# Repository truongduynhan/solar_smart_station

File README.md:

<h1 align="center">Balanced Solar Charger</h1>

<p align="center" width="100%">
  
</p>

***

<p align="center">
  
&nbsp; &nbsp; &nbsp; &nbsp;
  
</p>

***

## SPECIFICATIONS

| Parameter | Value | 
| --- | --- |
| Dimensions | 57.75 × 39.5 mm |

***

## DIRECTORY STRUCTURE

    .
    ├─ Computations       # Misc calculations
    ├─ HTML               # HTML files for generated webpage
    ├─ Images             # Pictures and renders
    │
    ├─ kibot_resources    # External resources for KiBot
    │  ├─ colors          # Color theme for KiCad
    │  ├─ fonts           # Fonts used in the project
    │  ├─ scripts         # External scripts used with KiBot
    │  └─ templates       # Templates for KiBot generated reports
    │
    ├─ kibot_yaml         # KiBot YAML config files
    ├─ KiRI               # KiRI (PCB diff viewer) files
    │
    ├─ lib                # KiCad footprint and symbol libraries
    │  ├─ 3d_models       # Component 3D models
    │  ├─ lib_fp          # Footprint libraries
    │  └─ lib_sym         # Symbol libraries
    │
    ├─ Logos              # Logos
    │
    ├─ Manufacturing      # Assembly and fabrication documents
    │  ├─ Assembly        # Assembly documents (BoM, pos, notes)
    │  │
    │  └─ Fabrication     # Fabrication documents (ZIP, notes)
    │     ├─ Drill Tables # CSV drill tables
    │     └─ Gerbers      # Gerbers
    │
    ├─ Report             # Reports for ERC/DRC
    ├─ Schematic          # PDF of schematic
    ├─ Templates          # Title block templates
    ├─ Testing
    │  └─ Testpoints      # Testpoints tables      
    │
    └─ Variants           # Outputs for assembly variants

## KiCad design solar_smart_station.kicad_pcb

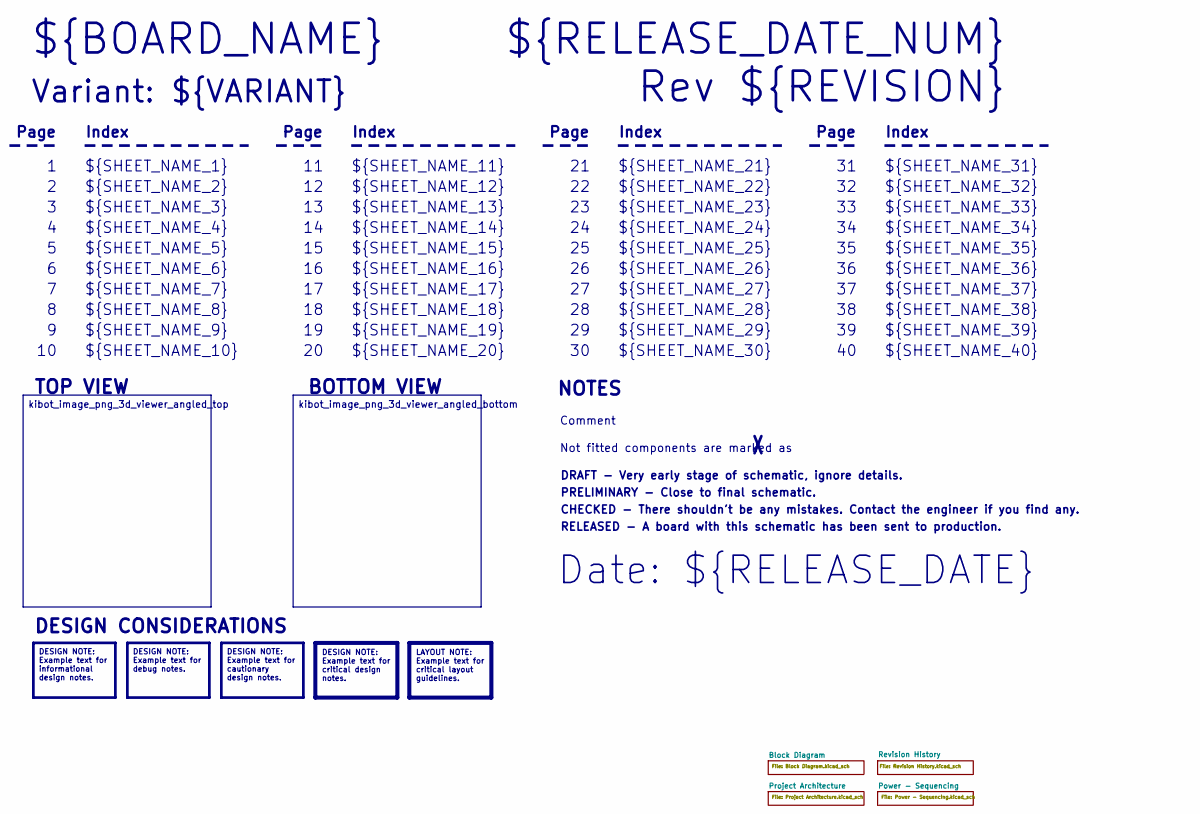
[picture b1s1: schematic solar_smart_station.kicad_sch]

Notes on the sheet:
Variant: ${VARIANT}
RELEASED - A board with this schematic has been sent to production.
${SHEET_NAME_24}
Index
Page
PRELIMINARY - Close to final schematic.
${SHEET_NAME_22}
DRAFT - Very early stage of schematic, ignore details.
${SHEET_NAME_12}
${SHEET_NAME_8}
${SHEET_NAME_2}
${SHEET_NAME_5}
${SHEET_NAME_20}
${SHEET_NAME_23}
${RELEASE_DATE_NUM}
${SHEET_NAME_35}
Not fitted components are marked as
${SHEET_NAME_11}
${SHEET_NAME_6}
${SHEET_NAME_37}
${SHEET_NAME_26}
${SHEET_NAME_36}
Rev ${REVISION}
${SHEET_NAME_15}
CHECKED - There shouldn't be any mistakes. Contact the engineer if you find any.
BOTTOM VIEW
${SHEET_NAME_14}
${SHEET_NAME_21}
${SHEET_NAME_17}
${SHEET_NAME_18}
Date: ${RELEASE_DATE}
${SHEET_NAME_7}
${SHEET_NAME_31}
${BOARD_NAME}
NOTES
${SHEET_NAME_40}
${SHEET_NAME_39}
${SHEET_NAME_32}
${SHEET_NAME_1}
${SHEET_NAME_9}

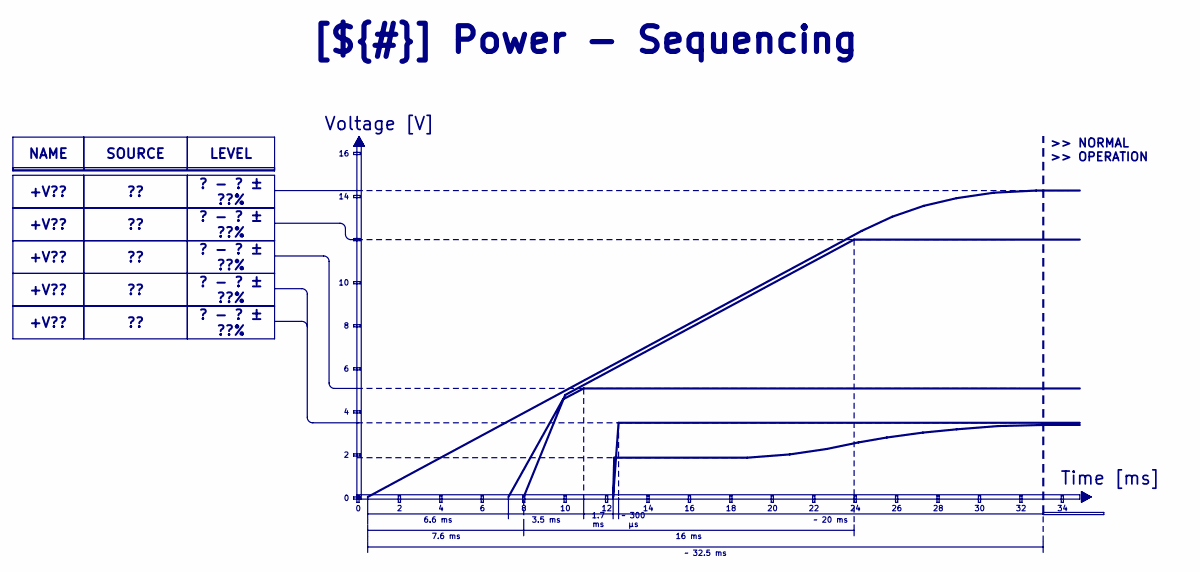
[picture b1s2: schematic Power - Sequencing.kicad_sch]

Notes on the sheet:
Voltage [V]
>> NORMAL >> OPERATION
Time [ms]
3.5 ms
7.6 ms
? - ? ± ??%
~ 300 μs
1.7 ms
16 ms
+V??
LEVEL
NAME
~ 20 ms
SOURCE
[${#}] ${TITLE}
6.6 ms
~ 32.5 ms

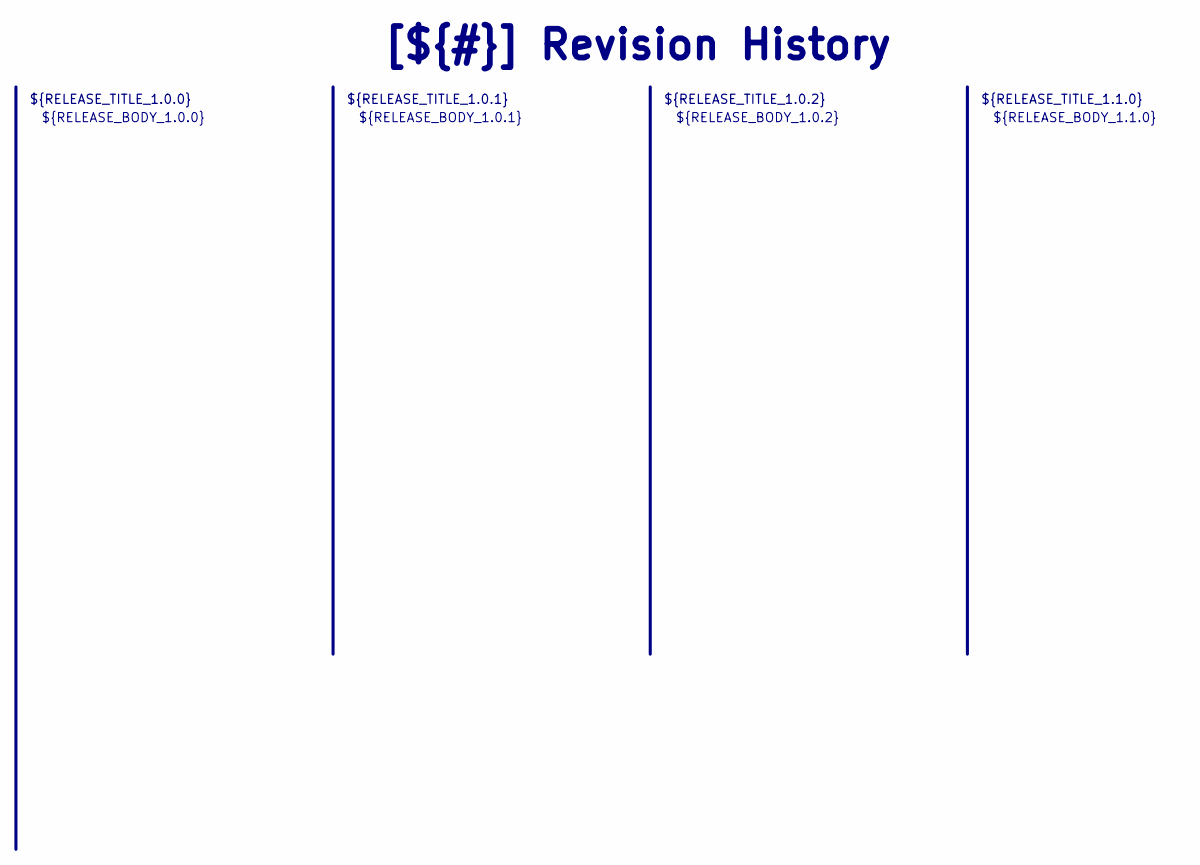
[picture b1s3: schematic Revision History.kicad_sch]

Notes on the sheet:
${RELEASE_BODY_1.1.0}
[${#}] ${TITLE}
${RELEASE_BODY_1.0.0}
${RELEASE_TITLE_1.0.2}
${RELEASE_BODY_1.0.2}
${RELEASE_BODY_1.0.1}
${RELEASE_TITLE_1.0.0}
${RELEASE_TITLE_1.0.1}
${RELEASE_TITLE_1.1.0}

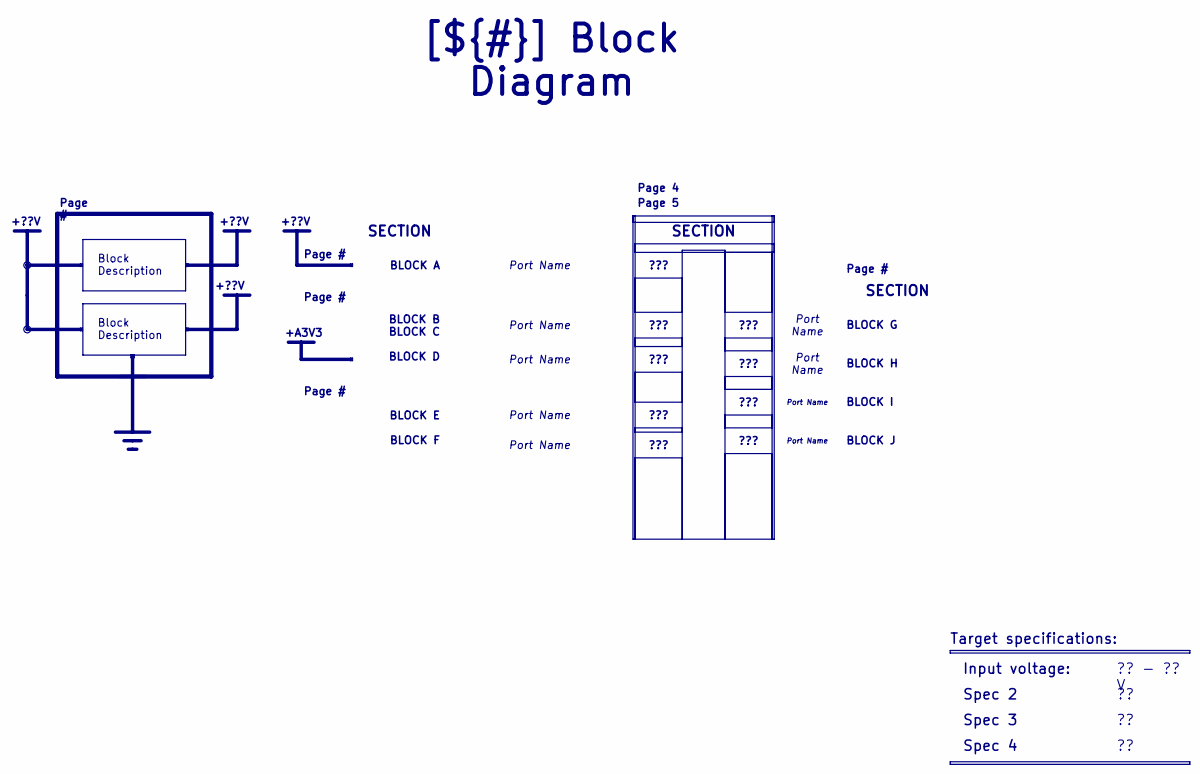
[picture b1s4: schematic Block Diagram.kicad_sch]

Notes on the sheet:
+??V
+A3V3
SECTION
Spec 4
BLOCK H
BLOCK B BLOCK C BLOCK D
BLOCK I
?? - ?? V
Block Description
???
Port Name
BLOCK G
Page #
Page 4
[${#}] ${TITLE}
Input voltage:
Target specifications:
Spec 3
Spec 2
BLOCK A
BLOCK E BLOCK F
BLOCK J
Page 5

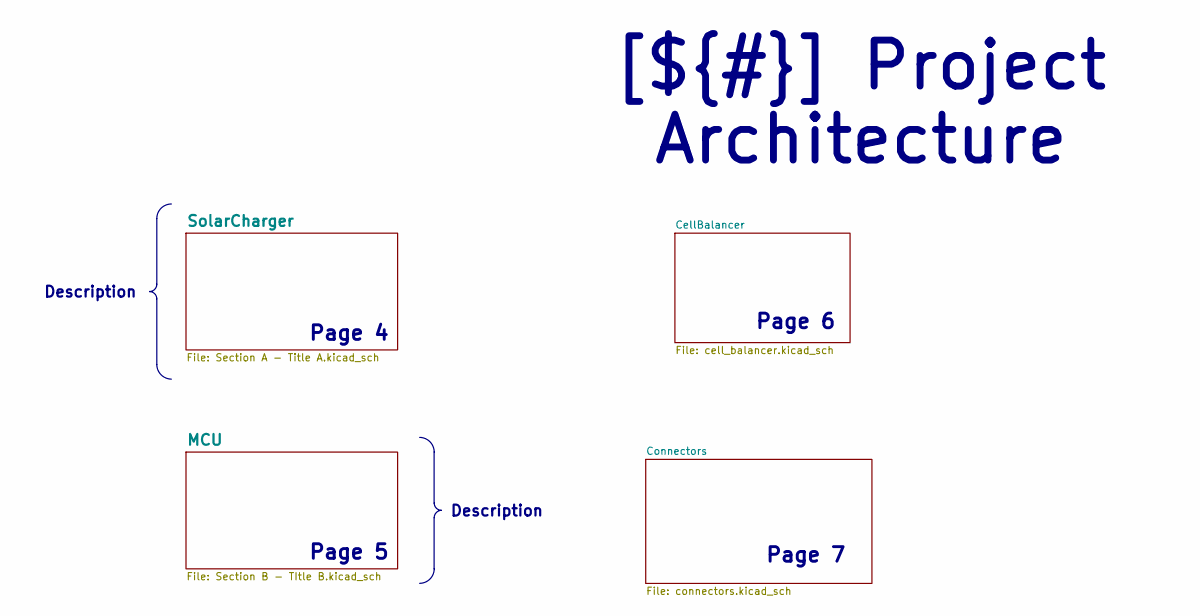
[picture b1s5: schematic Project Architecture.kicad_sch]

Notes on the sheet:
Page 6
Page 7
Page 5
Page 4
Description
[${#}] ${TITLE}

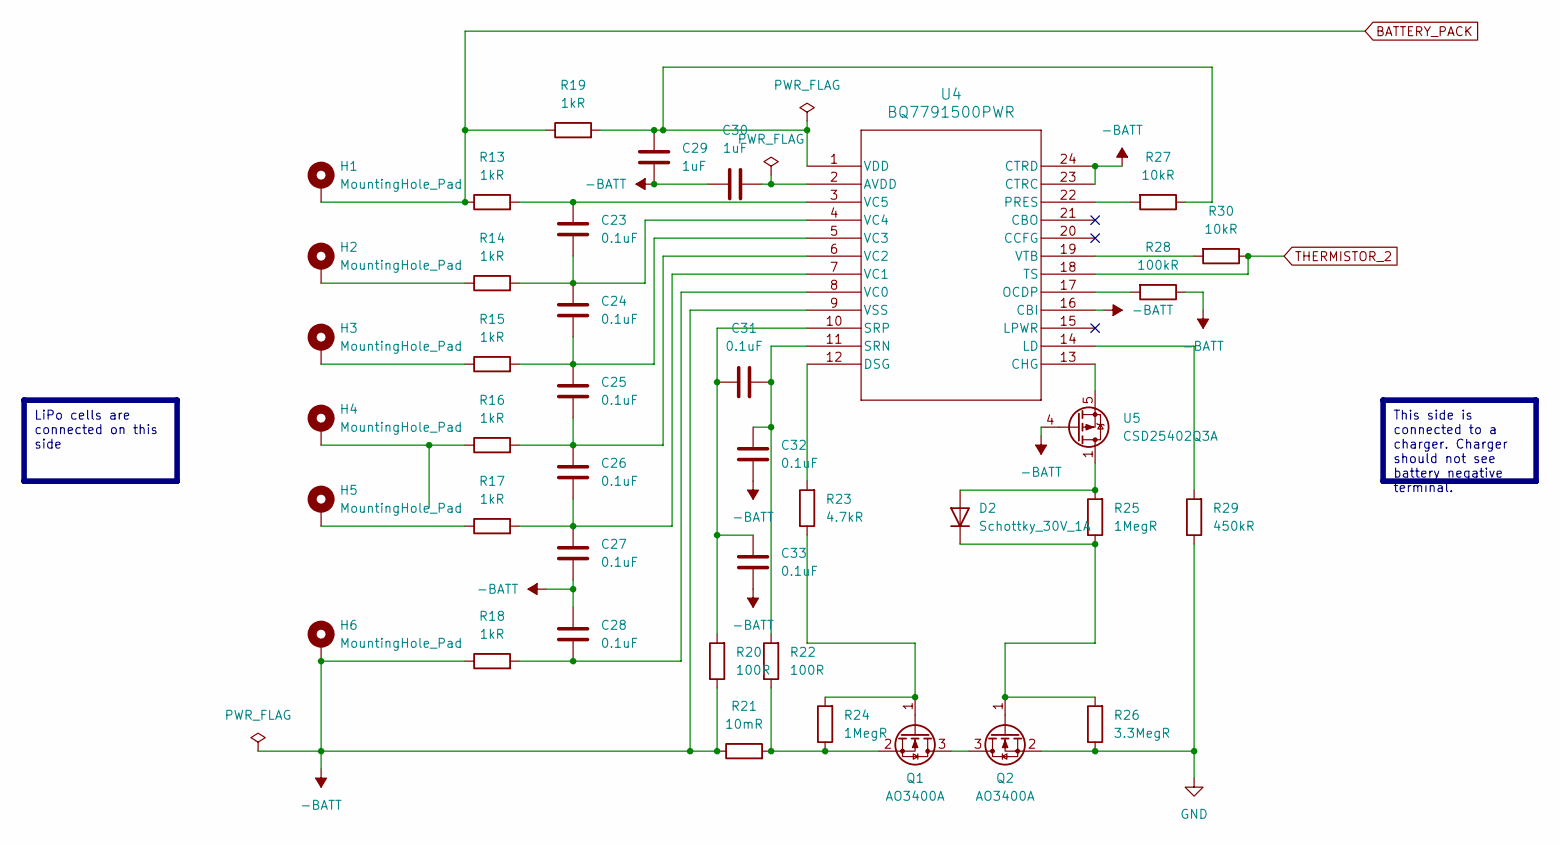
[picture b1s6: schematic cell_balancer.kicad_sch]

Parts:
C23, C24, C25, C26, C27, C28, C31, C32, C33: 0.1uF; C_0603_1608Metric; MPN TBD
C29, C30: 1uF; C_0603_1608Metric; MPN TBD
D2: Schottky_30V_1A; DIO_RB02_ROM; MPN RSX101VYM30FHTR
H1, H2, H3, H4, H5, H6: MountingHole_Pad; TestPoint_THTPad_2.5x2.5mm_Drill1.2mm
Q1, Q2: AO3400A; SOT-23
R13, R14, R15, R16, R17, R18, R19: 1kR; R_0402_1005Metric; MPN TBD
R20, R22: 100R; R_0402_1005Metric; MPN TBD
R21: 10mR; R_0805_2012Metric; MPN TBD
R23: 4.7kR; R_0402_1005Metric; MPN TBD
R24, R25: 1MegR; R_0402_1005Metric; MPN TBD
R26: 3.3MegR; R_0402_1005Metric; MPN TBD
R27, R30: 10kR; R_0402_1005Metric; MPN TBD
R28: 100kR; R_0402_1005Metric; MPN TBD
R29: 450kR; R_0402_1005Metric; MPN TBD
U4: BQ7791500PWR; PW24_TEX; MPN TBD
U5: CSD25402Q3A; VSON-8_3.3x3.3mm_P0.65mm_NexFET

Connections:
-BATT: C27.1, C28.2, C29.1, C30.1, C32.2, C33.2, H6.1, R18.1, R20.1, R21.1, R28.1, U4.9 (VSS), U4.16 (CBI), U4.23 (CTRC), U4.24 (CTRD), U5.4 (G)
BATTERY_PACK: H1.1, R13.1, R19.1; also elsewhere on the board
GND: Q2.2 (S), R26.1, R29.1; also elsewhere on the board
unnamed: D2.2 (A), R25.2, U5.1 (D), U5.2 (D), U5.3 (D)
unnamed: D2.1 (K), Q2.1 (G), R25.1, R26.2
unnamed: H2.1, R14.1
unnamed: H3.1, R15.1
unnamed: H4.1, R16.1
unnamed: H5.1, R17.1
unnamed: Q1.3 (D), Q2.3 (D)
unnamed: Q1.1 (G), R23.1, R24.2
unnamed: Q1.2 (S), R21.2, R22.1, R24.1
unnamed: C30.2, U4.2 (AVDD)
unnamed: U4.13 (CHG), U5.5 (S)
unnamed: R23.2, U4.12 (DSG)
unnamed: R29.2, U4.14 (LD)
unnamed: R28.2, U4.17 (OCDP)
unnamed: R27.2, U4.22 (PRES)
unnamed: C31.1, C32.1, R22.2, U4.11 (SRN)
unnamed: C31.2, C33.1, R20.2, U4.10 (SRP)
unnamed: C28.1, R18.2, U4.8 (VC0)
unnamed: C26.1, C27.2, R17.2, U4.7 (VC1)
unnamed: C25.1, C26.2, R16.2, U4.6 (VC2)
unnamed: C24.1, C25.2, R15.2, U4.5 (VC3)
unnamed: C23.1, C24.2, R14.2, U4.4 (VC4)
unnamed: C23.2, R13.2, U4.3 (VC5)
unnamed: C29.2, R19.2, R27.1, U4.1 (VDD)
unnamed: R30.2, U4.19 (VTB)
THERMISTOR_2: R30.1, U4.18 (TS); also elsewhere on the board

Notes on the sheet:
LiPo cells are connected on this side
This side is connected to a charger. Charger should not see battery negative terminal.

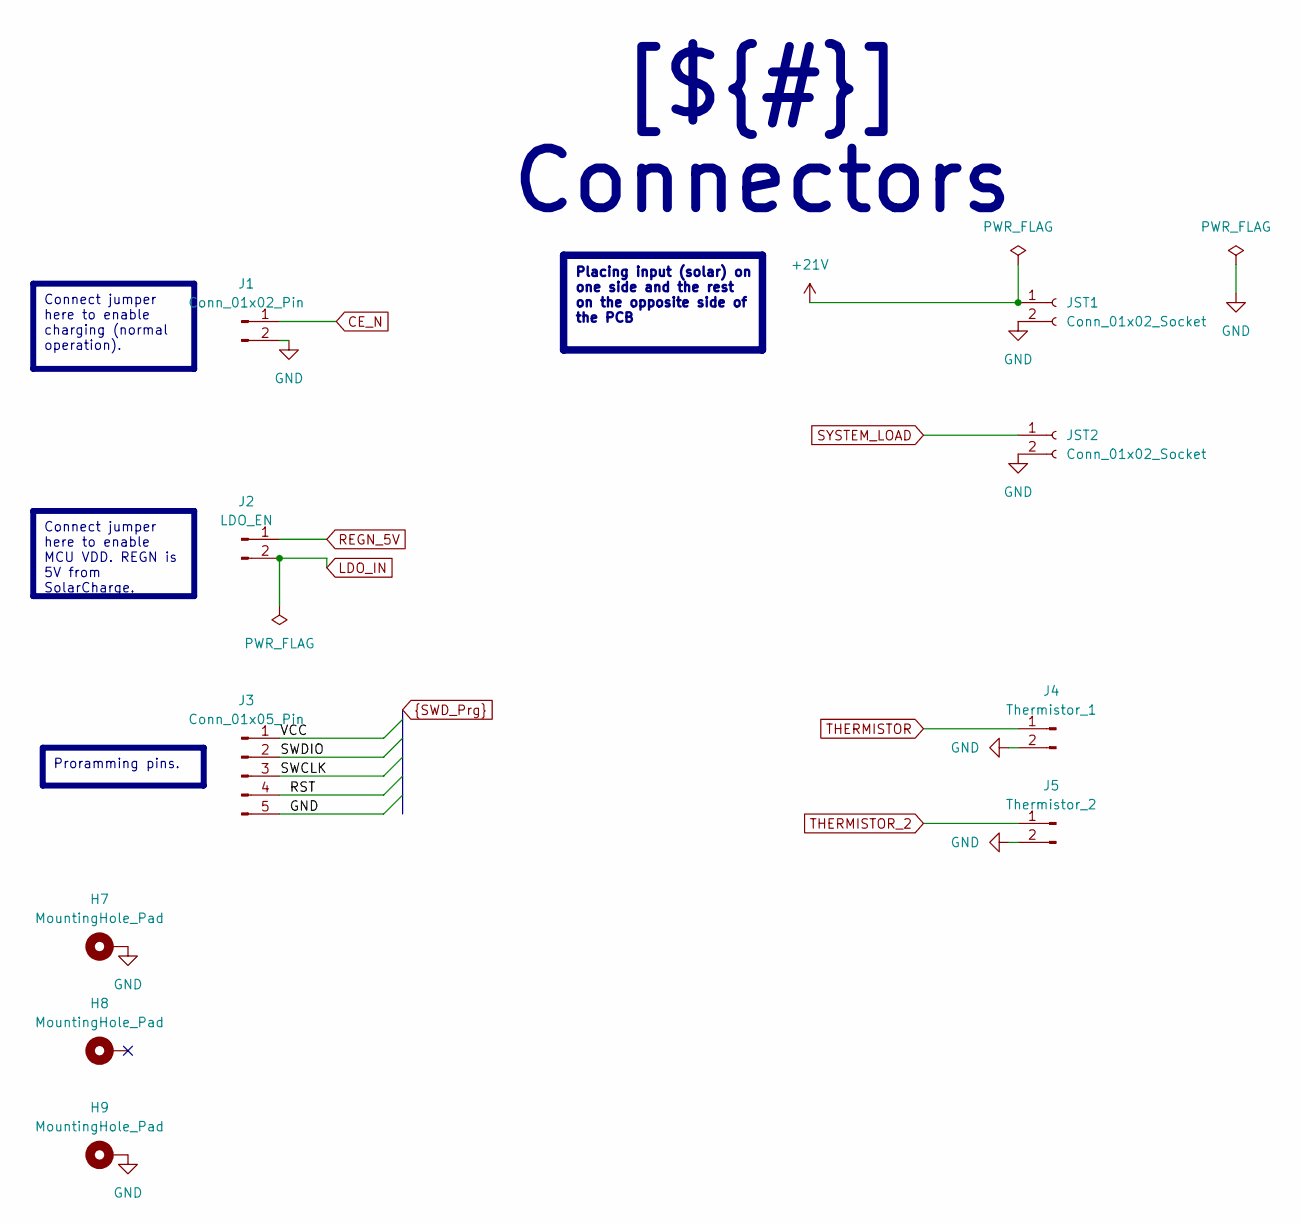
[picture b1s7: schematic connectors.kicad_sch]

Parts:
H7, H8, H9: MountingHole_Pad; MountingHole_3.2mm_M3_DIN965_Pad_TopBottom
J1: Conn_01x02_Pin; PinHeader_1x02_P2.54mm_Vertical
J2: LDO_EN; PinHeader_1x02_P2.54mm_Vertical
J3: Conn_01x05_Pin; PinHeader_1x05_P2.54mm_Vertical
J4: Thermistor_1; PinHeader_1x02_P2.54mm_Vertical
J5: Thermistor_2; PinHeader_1x02_P2.54mm_Vertical
JST1, JST2: Conn_01x02_Socket; JST_VH_B2P-VH_1x02_P3.96mm_Vertical

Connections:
+21V: JST1.1; also elsewhere on the board
CE_N: J1.1; also elsewhere on the board
GND: H7.1, H9.1, J1.2, J3.5, J4.2, J5.2, JST1.2, JST2.2; also elsewhere on the board
LDO_IN: J2.2; also elsewhere on the board
REGN_5V: J2.1; also elsewhere on the board
RST: J3.4; also elsewhere on the board
SWCLK: J3.3; also elsewhere on the board
SWDIO: J3.2; also elsewhere on the board
SYSTEM_LOAD: JST2.1; also elsewhere on the board
THERMISTOR: J4.1; also elsewhere on the board
THERMISTOR_2: J5.1; also elsewhere on the board
VCC: J3.1; also elsewhere on the board

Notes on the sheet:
Placing input (solar) on one side and the rest on the opposite side of the PCB
Connect jumper here to enable charging (normal operation).
Proramming pins.
[${#}] ${TITLE}
Connect jumper here to enable MCU VDD. REGN is 5V from SolarCharge.

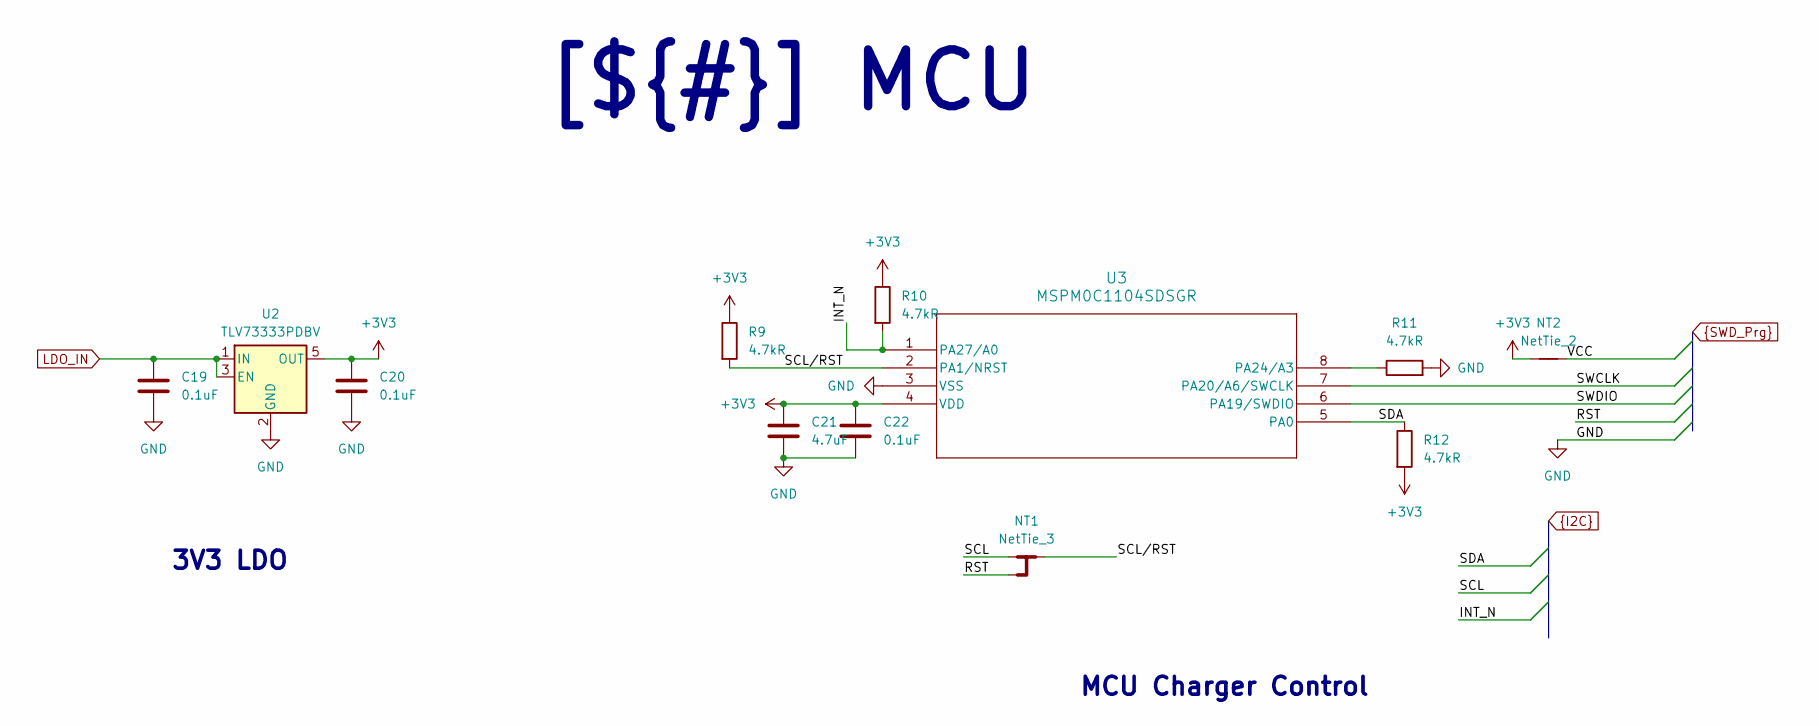
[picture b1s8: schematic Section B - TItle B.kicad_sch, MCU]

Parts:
C19, C20, C22: 0.1uF; C_0603_1608Metric; MPN TBD
C21: 4.7uF; C_0603_1608Metric; MPN TBD
NT1: NetTie_3; NetTie-3_SMD_Pad0.5mm
NT2: NetTie_2; NetTie-2_SMD_Pad0.5mm
R9, R10, R11, R12: 4.7kR; R_0402_1005Metric; MPN TBD
U2: TLV73333PDBV; SOT-23-5
U3: MSPM0C1104SDSGR; TSOT-23-8-shrink

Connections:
+3V3: C20.2, C21.2, C22.2, NT2.1, R9.1, R10.1, R12.2, U2.5 (OUT), U3.4 (VDD)
/Project Architecture/MCU/SCL/RST: NT1.2, R9.2, U3.2 (PA1/NRST)
GND: C19.1, C20.1, C21.1, C22.1, R11.2, U2.2 (GND), U3.3 (VSS); also elsewhere on the board
INT_N: R10.2, U3.1 (PA27/A0); also elsewhere on the board
LDO_IN: C19.2, U2.1 (IN), U2.3 (EN); also elsewhere on the board
unnamed: R11.1, U3.8 (PA24/A3)
RST: NT1.3; also elsewhere on the board
SCL: NT1.1; also elsewhere on the board
SDA: R12.1, U3.5 (PA0); also elsewhere on the board
SWCLK: U3.7 (PA20/A6/SWCLK); also elsewhere on the board
SWDIO: U3.6 (PA19/SWDIO); also elsewhere on the board
VCC: NT2.2; also elsewhere on the board

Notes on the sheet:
[${#}] ${TITLE}
MCU Charger Control
3V3 LDO

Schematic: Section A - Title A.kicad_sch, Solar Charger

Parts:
C1: 2.2uF; C_0805_2012Metric; MPN TBD
C2, C9, C10: 0.1uF; C_0402_1005Metric; MPN TBD
C3, C4, C11, C12, C13, C14, C15, C16, C17, C18: 10uF; C_1206_3216Metric; MPN TBD
C5, C7: 47nF; C_0402_1005Metric; MPN TBD
C6: 4.7uF; C_0603_1608Metric; MPN TBD
C8: 1nF; C_0402_1005Metric; MPN TBD
D1: LED; LED_0603_1608Metric
L1: 1uH; L_Bourns_SRP7028A_7.3x6.6mm; MPN SPM6530T-1R0M120
R1: 2R-1W; R_2010_5025Metric; MPN TBD
R2: 4.7kR; R_0402_1005Metric; MPN TBD
R3: 5.24kR; R_0402_1005Metric; MPN TBD
R4: 30.31kR; R_0402_1005Metric; MPN TBD
R5: 6.04kR; R_0402_1005Metric; MPN TBD
R6: 100R; R_0402_1005Metric; MPN TBD
R7: 127kR; R_0402_1005Metric; MPN TBD
R8: 100kR; R_0402_1005Metric; MPN TBD
TP1: QON; PinHeader_1x01_P2.54mm_Vertical
U1: BQ25672RQMR; RQM0029A-MFG; MPN TBD

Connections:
+21V: C2.2, C3.2, C4.2, R1.1, U1.2 (VBUS), U1.3 (VBUS), U1.8 (VAC2), U1.9 (VAC1); also elsewhere on the board
/Project Architecture/SolarCharger/QON: TP1.1, U1.12 (QON_N)
BATTERY_PACK: C11.2, C14.2, R6.2, U1.22 (BAT), U1.23 (BAT); also elsewhere on the board
CE_N: U1.13 (CE_N); also elsewhere on the board
GND: C1.2, C2.1, C3.1, C4.1, C6.1, C8.2, C9.1, C10.1, C11.1, C12.1, C13.1, C14.1, C15.1, C16.1, C17.1, C18.1, R4.1, R5.2, R8.1, U1.10 (ACDRV2), U1.11 (ACDRV1), U1.27 (GND); also elsewhere on the board
INT_N: U1.21 (INT_N); also elsewhere on the board
unnamed: C1.1, R1.2
unnamed: D1.2 (A), R2.2
unnamed: D1.1 (K), U1.1 (STAT)
unnamed: R6.1, U1.18 (BATP)
unnamed: C5.1, U1.4 (BTST1)
unnamed: C7.2, U1.19 (BTST2)
unnamed: R7.1, R8.2, U1.17 (ILIM_HIZ)
unnamed: C9.2, C12.2, C15.2, C17.2, U1.29 (PMID)
unnamed: R5.1, U1.20 (PROG)
unnamed: C8.1, U1.24 (SDRV)
unnamed: C5.2, L1.1, U1.28 (SW1)
unnamed: C7.1, L1.2, U1.26 (SW2)
REGN_5V: C6.2, R2.1, R3.2, R7.2, U1.5 (REGN); also elsewhere on the board
SCL: U1.14 (SCL); also elsewhere on the board
SDA: U1.15 (SDA); also elsewhere on the board
SYSTEM_LOAD: C10.2, C13.2, C16.2, C18.2, U1.25 (SYS); also elsewhere on the board
THERMISTOR: R3.1, R4.2, U1.16 (TS); also elsewhere on the board

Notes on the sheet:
[${#}] ${TITLE}

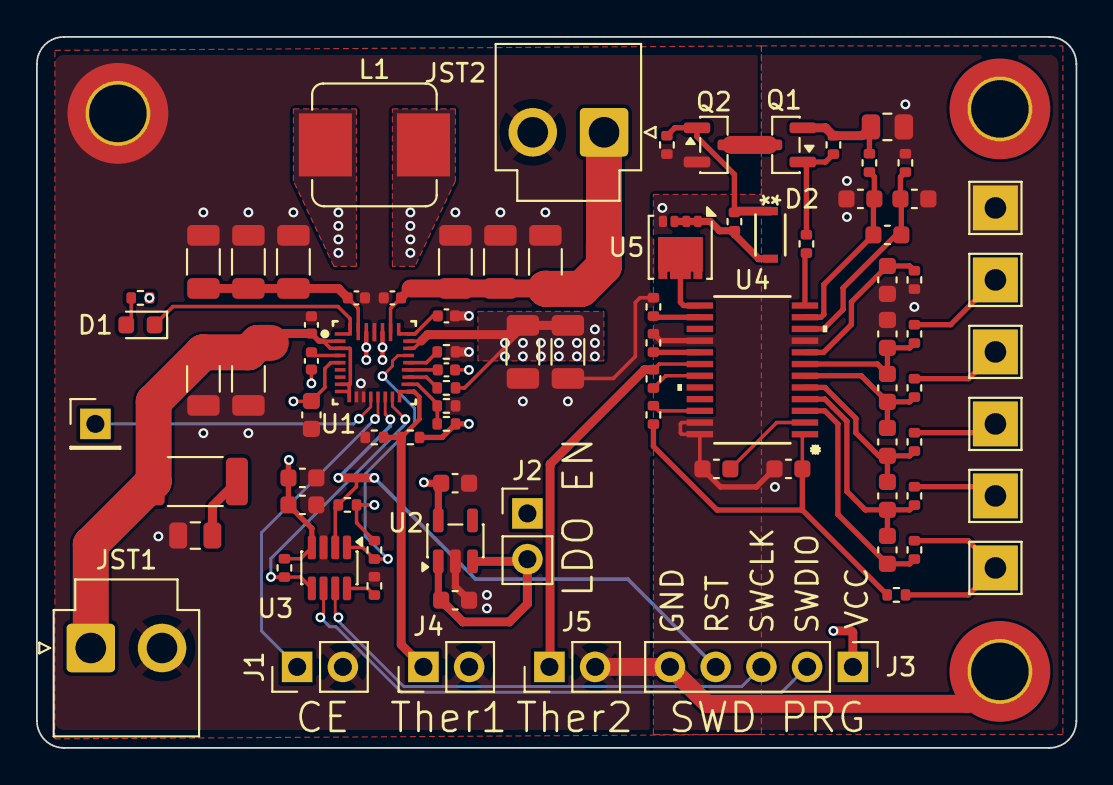
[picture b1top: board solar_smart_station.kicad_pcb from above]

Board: 4 copper layers, 57.8 x 39.5 mm, 92 parts (0 on the bottom side), 58 nets.

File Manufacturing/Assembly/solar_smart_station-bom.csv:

Row,Quantity Per PCB,References,Value,Datasheet,Footprint,Description,Manufacturer,MPN,Supplier Part Number
1,1,C8,1nF,~,C_0402_1005Metric,Unpolarized capacitor,,TBD,
2,2,C5 C7,47nF,~,C_0402_1005Metric,Unpolarized capacitor,,TBD,
3,15,C2 C9 C10 C19 C20 C22 C23 C24 C25 C26 C27 C28 C31 C32 C33,0.1uF,~,C_0402_1005Metric,Unpolarized capacitor,,TBD,
4,2,C29 C30,1uF,~,C_0603_1608Metric,Unpolarized capacitor,,TBD,
5,1,C1,2.2uF,~,C_0805_2012Metric,Unpolarized capacitor,,TBD,
6,2,C6 C21,4.7uF,~,C_0603_1608Metric,Unpolarized capacitor,,TBD,
7,10,C3 C4 C11 C12 C13 C14 C15 C16 C17 C18,10uF,~,C_1206_3216Metric,Unpolarized capacitor,,TBD,
8,1,D1,LED,~,LED_0603_1608Metric,Light emitting diode,,,
9,1,D2,Schottky_30V_1A,,DIO_RB02_ROM,DIODE SCHOTTKY 30V 1A TUMD2M,,RSX101VYM30FHTR,
10,7,J1 J2 J3 J4 J5 JST1 JST2,Conn_01x02_Pin,~,PinHeader_1x02_P2.54mm_Vertical,"Generic connector, single row, 01x02, script generated Generic connector, single row, 01x05, script generated",,,
11,1,L1,1uH,~,L_Bourns_SRP7028A_7.3x6.6mm,Inductor,,SPM6530T-1R0M120,
12,2,Q1 Q2,AO3400A,http://www.aosmd.com/pdfs/datasheet/AO3400A.pdf,SOT-23,"30V Vds, 5.7A Id, N-Channel MOSFET, SOT-23",,,
13,1,R21,10mR,~,R_0805_2012Metric,Resistor,,TBD,
14,3,R6 R20 R22,100R,~,R_0402_1005Metric,Resistor,,TBD,
15,7,R13 R14 R15 R16 R17 R18 R19,1kR,~,R_0402_1005Metric,Resistor,,TBD,
16,6,R2 R9 R10 R11 R12 R23,4.7kR,~,R_0402_1005Metric,Resistor,,TBD,
17,1,R3,5.24kR,~,R_0402_1005Metric,Resistor,,TBD,
18,1,R5,6.04kR,~,R_0402_1005Metric,Resistor,,TBD,
19,2,R27 R30,10kR,~,R_0402_1005Metric,Resistor,,TBD,
20,1,R4,30.31kR,~,R_0402_1005Metric,Resistor,,TBD,
21,2,R8 R28,100kR,~,R_0402_1005Metric,Resistor,,TBD,
22,1,R7,127kR,~,R_0402_1005Metric,Resistor,,TBD,
23,1,R29,450kR,~,R_0402_1005Metric,Resistor,,TBD,
24,2,R24 R25,1MegR,~,R_0402_1005Metric,Resistor,,TBD,
25,1,R26,3.3MegR,~,R_0402_1005Metric,Resistor,,TBD,
26,1,R1,2R-1W,~,R_2010_5025Metric,Resistor,,TBD,
27,1,U1,BQ25672RQMR,https://www.ti.com/lit/gpn/bq25672,RQM0029A-MFG,,,TBD,
28,1,U4,BQ7791500PWR,https://www.ti.com/lit/gpn/bq77915,PW24_TEX,,,TBD,
29,1,U5,CSD25402Q3A,https://www.ti.com/lit/ds/symlink/csd25402q3a.pdf,VSON-8_3.3x3.3mm_P0.65mm_NexFET,"-76A Id, -20V Vds, NexFET P-Channel Power MOSFET, 7.7mOhm Ron, Qg (typ) 7.5 nC, VSON-8 3.3x3.3mm",,,
30,1,U3,MSPM0C1104SDSGR,https://www.ti.com/lit/gpn/mspm0c1104,TSOT-23-8-shrink,,,,
31,1,U2,TLV73333PDBV,http://www.ti.com/lit/ds/symlink/tlv733p.pdf,SOT-23-5,"300mA Capacitor-Free Low Dropout Voltage Regulator, Fixed Output 3.3V, SOT-23-5",,,

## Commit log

2026-01-04 Create template
2026-01-04 Update Outputs
2026-01-06 First draft of schematic
2026-01-06 Change schematic sheet size to A4
2026-01-06 Change bom yaml to MPN
2026-01-07 Add cell balancer - in progress
2026-01-08 Finish schematic
2026-01-08 First layout
2026-01-09 Finish layout
2026-01-09 Fix ERC
2026-01-09 All connectors are deemed the same in BOM. Re-push.
2026-01-09 Change J1 value to fix BOM
2026-01-09 Replace jumper to force BOM updated
2026-01-09 Finish checking - Ready for 1st release
2026-01-09 Ready for 1st release
2026-01-09 Release 1.0.0
2026-01-09 Update CHANGELOG
2026-01-09 Update Outputs (release)
2026-01-30 Update PCB origin
